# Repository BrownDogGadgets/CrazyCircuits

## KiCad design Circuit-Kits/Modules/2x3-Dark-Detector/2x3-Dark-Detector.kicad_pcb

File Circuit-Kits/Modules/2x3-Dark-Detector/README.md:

<!--- start title --->
# 2x3 Dark Detector Module v1.0
A Lego-compatible Crazy Circuits module

- Updated: 24 Sep 2018

- Website: http://browndoggadgets.com/
- Company: Brown Dog Gadgets
- License: CERN Open Hardware License v1.2
<!--- end title --->

This circuit applies 3V to turn a transistor on and off, based on whether the on-board photocell detects light. The output will go high if there is no light.

<!--- bom start --->
## Bill of Materials

|Ref|Qty|Description|Digikey PN|
|---|---|-----------|------|
|LDR1|1|PHOTOTRANSISTOR FLAT BK MINI SMD|1080-1383-1-ND|
|Q1|1|TRANS NPN 40V 0.2A SOT-23|MMBT3904TPMSCT-ND|
|R1|1|RES SMD 100K OHM 5% 1/10W 0603|311-100KGRCT-ND|

<!--- bom end --->

### Manufacturing Notes

This board must be v-scored. Do not panelize with support tabs or mousebites.

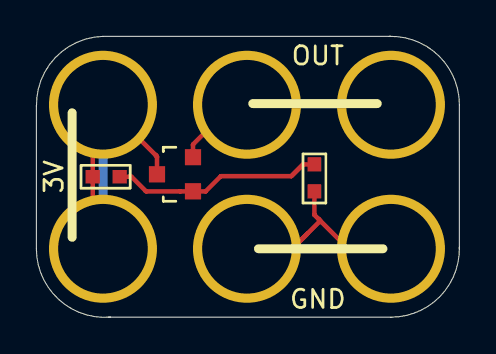
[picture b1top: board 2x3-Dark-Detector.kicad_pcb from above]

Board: 2 copper layers, 23.5 x 15.6 mm, 3 parts (0 on the bottom side), 2 nets.

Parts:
LDR1: PHOTOCELL; RLC-0603-SMD
Q1: NPN MMBT3904; SOT-23-3
R1: 100K; RLC-0603-SMD

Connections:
3V: Q1.3, R1.1
unnamed: LDR1.2, Q1.1, R1.2

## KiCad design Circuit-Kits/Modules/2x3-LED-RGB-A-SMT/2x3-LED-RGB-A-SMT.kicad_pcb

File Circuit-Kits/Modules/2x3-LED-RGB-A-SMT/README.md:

<!--- start title --->
# 2x3 LED RGB (A) SMT v1.1
A Lego-compatible Crazy Circuits module

- Updated: 31 May 2018

- Website: http://browndoggadgets.com/
- Company: Brown Dog Gadgets
- License: CERN Open Hardware License v1.2.
<!--- end title --->

Surface mount RGB LED with a common anode. Connect the Common (C) to 3.3V.

<!--- bom start --->
### Bill of Materials

|Ref|Qty|Description|Digikey PN|
|---|---|-----------|------|
|LED1|1|LED CHIP RGB 19-237 A01/2T SMD |19-237/R6GHBHC-A01/2T-ND|
|R1 R2|2|RES SMD 100 OHM 1% 1/10W 0603|A106047CT-ND|
|R3|1|RES 47 OHM 5% 1/10W 0603|311-47GRCT-ND|

<!--- bom end --->

### Manufacturing Notes

This board must be v-scored. Do not panelize with support tabs or mousebites.

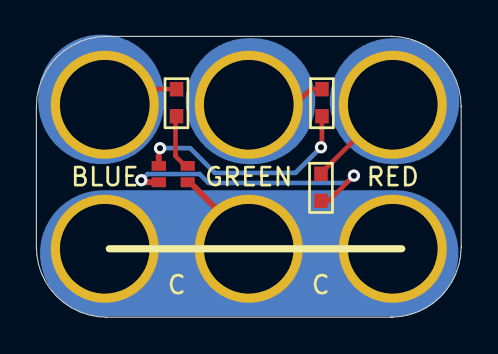
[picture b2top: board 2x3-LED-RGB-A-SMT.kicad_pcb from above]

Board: 2 copper layers, 23.6 x 15.6 mm, 4 parts (0 on the bottom side), 3 nets.

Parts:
LED1: LED-RGB-SMT-19-237-RGB; LED-RGB-0606-19-237-2x3
R1, R2: 100; RLC-0603-SMD
R3: 47; RLC-0603-SMD

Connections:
/B: LED1.3, R3.1
/G: LED1.2, R2.1
/R: LED1.1, R1.1

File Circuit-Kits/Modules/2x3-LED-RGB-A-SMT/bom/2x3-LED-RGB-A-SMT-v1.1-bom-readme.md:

|Ref|Qty|Description|Digikey PN|
|---|---|-----------|------|
|LED1|1|LED CHIP RGB 19-237 0606 SMD |1080-1590-1-ND|
|R1 R2|2|RES SMD 100 OHM 1% 1/10W 0603|A106047CT-ND|
|R3|1|RES 47 OHM 5% 1/10W 0603|311-47GRCT-ND|

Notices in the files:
Circuit-Kits/Modules/2x3-Dark-Detector/2x3-Dark-Detector.kicad_pcb:
All rights reserved.
